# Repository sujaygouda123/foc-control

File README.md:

# FOC CONTROL REV A

BLDC field-oriented-control board for a humanoid robot actuator. KiCad 10, Ø80 mm, 8 layers, 1.6 mm.

| Top | Bottom |
|---|---|
|  |  |

## Main parts

| Function | Part |
|---|---|
| MCU | STM32G474RET3 |
| Gate driver | DRV8353S |
| MOSFETs | 6 × BSC040N10NS5 (100 V, 4 mΩ) |
| Current sensing | 3 × 1 mΩ low-side shunts |
| Position | AS5047P magnetic encoder (bottom side) |
| CAN FD | MCP2562FD, 2 × XT30PW 2+2 (power + CAN) |
| Supplies | 2 × LM5164 (12 V, 5 V), AP2112K (3.3 V) |

## Stage 1 – single actuator

## Stage 2 – multiple actuators

- One cable per link: VBUS + GND (16 AWG) and CAN-H / CAN-L as a twisted pair.
- Two XT30 2+2 connectors per board (IN, OUT), 15 A continuous.
- 120 Ω termination only at the two ends of each bus (JP1 on the last actuator).

## Stackup

| Layer | Use |
|---|---|
| F.Cu, 2 oz | Components, power pours |
| In1 | GND |
| In2 | Signals |
| In3 | VBUS |
| In4 | GND |
| In5 | Signals |
| In6 | GND |
| B.Cu, 2 oz | Phase pours, encoder |

Inner layers are 1 oz. Power runs on the 2 oz outer layers; every signal layer sits next to a plane.

## JLCPCB rules

| Rule | JLCPCB minimum (2 oz) | This board |
|---|---|---|
| Track / gap | 0.15 / 0.15 mm | 0.2 / 0.15 mm (0.15 mm only at fine-pitch pins) |
| Via diameter / hole | 0.25 / 0.15 mm | 0.45 / 0.2 mm |
| Copper to board edge | 0.2 mm | 0.5 mm |

## Trace widths

| Net class | Width | Gap |
|---|---|---|
| Signals | 0.2 mm | 0.15 mm |
| Gate drive | 0.3 mm | 0.15 mm |
| High voltage (VBUS, phases) | 0.5 mm, power in pours | 0.2 mm |
| CAN pair | 0.2 mm | 0.2 mm between the pair |

## File structure

```
foc-control/
├── foc-control.kicad_pro        KiCad 10 project (open this)
├── foc-control.kicad_sch        Root schematic (links the 6 sheets below)
├── can_connectors.kicad_sch     XT30 connectors, MCP2562FD CAN FD transceiver, termination
├── encoder.kicad_sch            AS5047P magnetic encoder
├── MCU.kicad_sch                STM32G474, clock, decoupling, reset/boot, SWD pads
├── power_rails.kicad_sch        12 V and 5 V bucks (LM5164), 3.3 V LDO
├── gate_driver.kicad_sch        DRV8353 gate driver
├── power_stage.kicad_sch        3 half-bridges, shunts, bus capacitors, VBUS sense, NTC
├── foc-control.kicad_pcb        Ø80 mm, 8-layer board layout
├── fp-lib-table                 Project footprint libraries (points to libs/)
├── sym-lib-table                Project symbol libraries (points to libs/)
├── libs/
│   ├── foc-control.kicad_sym    DRV8353 symbol
│   ├── DRV8353.pretty/          DRV8353 footprint (WQFN-40)
│   ├── XT30/                    XT30PW 2+2 symbol, footprint and 3D model
│   └── logo.pretty/             Board logo
├── bom/
│   └── foc-control.csv          Bill of materials
└── docs/
    ├── Stage1/Stage1.drawio.png Stage 1 block diagram (single actuator)
    ├── Stage2/Stage2.drawio.png Stage 2 wiring diagram (multiple actuators)
    └── img/                     3D renders of the board (top, bottom)
```

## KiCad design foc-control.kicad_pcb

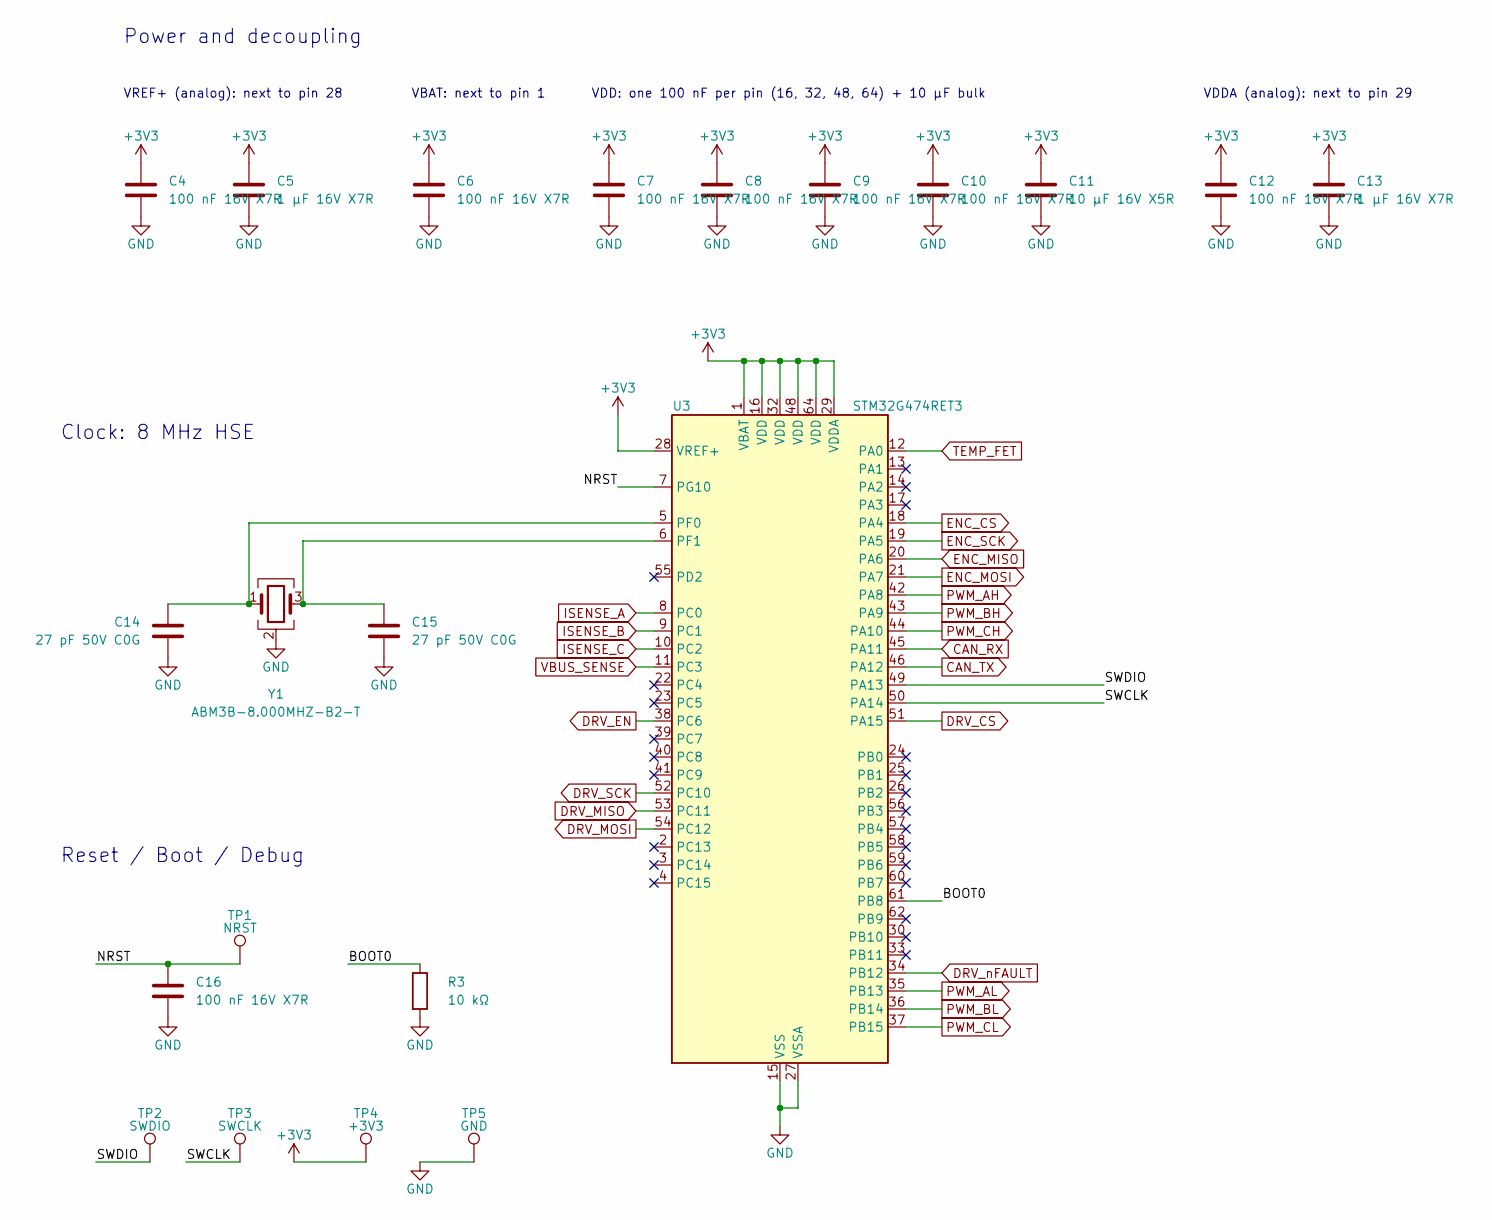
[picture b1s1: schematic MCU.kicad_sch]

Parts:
C4, C6, C7, C8, C9, C10, C12, C16: 100 nF 16V X7R; C_0603_1608Metric
C5, C13: 1 µF 16V X7R; C_0603_1608Metric
C11: 10 µF 16V X5R; C_0603_1608Metric
C14, C15: 27 pF 50V C0G; C_0603_1608Metric
R3: 10 kΩ; R_0603_1608Metric
TP1: NRST; TestPoint_Pad_D1.0mm
TP2: SWDIO; TestPoint_Pad_D1.0mm
TP3: SWCLK; TestPoint_Pad_D1.0mm
TP4: +3V3; TestPoint_Pad_D1.0mm
TP5: GND; TestPoint_Pad_D1.0mm
U3: STM32G474RET3; LQFP-64_10x10mm_P0.5mm
Y1: ABM3B-8.000MHZ-B2-T; Crystal_SMD_Abracon_ABM3B-4Pin_5.0x3.2mm

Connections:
+3V3: C4.1, C5.1, C6.1, C7.1, C8.1, C9.1, C10.1, C11.1, C12.1, C13.1, TP4.1 (1_1), U3.1 (VBAT), U3.16 (VDD), U3.28 (VREF+), U3.29 (VDDA), U3.32 (VDD), U3.48 (VDD), U3.64 (VDD); also elsewhere on the board
/MCU/BOOT0: R3.1, U3.61 (PB8)
/MCU/NRST: C16.1, TP1.1 (1_1), U3.7 (PG10)
/MCU/SWCLK: TP3.1 (1_1), U3.50 (PA14)
/MCU/SWDIO: TP2.1 (1_1), U3.49 (PA13)
CAN_RX: U3.45 (PA11); also elsewhere on the board
CAN_TX: U3.46 (PA12); also elsewhere on the board
DRV_CS: U3.51 (PA15); also elsewhere on the board
DRV_EN: U3.38 (PC6); also elsewhere on the board
DRV_MISO: U3.53 (PC11); also elsewhere on the board
DRV_MOSI: U3.54 (PC12); also elsewhere on the board
DRV_SCK: U3.52 (PC10); also elsewhere on the board
DRV_nFAULT: U3.34 (PB12); also elsewhere on the board
ENC_CS: U3.18 (PA4); also elsewhere on the board
ENC_MISO: U3.20 (PA6); also elsewhere on the board
ENC_MOSI: U3.21 (PA7); also elsewhere on the board
ENC_SCK: U3.19 (PA5); also elsewhere on the board
GND: C4.2, C5.2, C6.2, C7.2, C8.2, C9.2, C10.2, C11.2, C12.2, C13.2, C14.2, C15.2, C16.2, R3.2, TP5.1 (1_1), U3.15 (VSS), U3.27 (VSSA), U3.31 (VSS), U3.47 (VSS), U3.63 (VSS), Y1.2 (G), Y1.4 (G); also elsewhere on the board
ISENSE_A: U3.8 (PC0); also elsewhere on the board
ISENSE_B: U3.9 (PC1); also elsewhere on the board
ISENSE_C: U3.10 (PC2); also elsewhere on the board
unnamed: C14.1, U3.5 (PF0), Y1.1
unnamed: C15.1, U3.6 (PF1), Y1.3
PWM_AH: U3.42 (PA8); also elsewhere on the board
PWM_AL: U3.35 (PB13); also elsewhere on the board
PWM_BH: U3.43 (PA9); also elsewhere on the board
PWM_BL: U3.36 (PB14); also elsewhere on the board
PWM_CH: U3.44 (PA10); also elsewhere on the board
PWM_CL: U3.37 (PB15); also elsewhere on the board
TEMP_FET: U3.12 (PA0); also elsewhere on the board
VBUS_SENSE: U3.11 (PC3); also elsewhere on the board

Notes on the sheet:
Power and decoupling
Clock: 8 MHz HSE
VDDA (analog): next to pin 29
VREF+ (analog): next to pin 28
VBAT: next to pin 1
Reset / Boot / Debug
VDD: one 100 nF per pin (16, 32, 48, 64) + 10 µF bulk

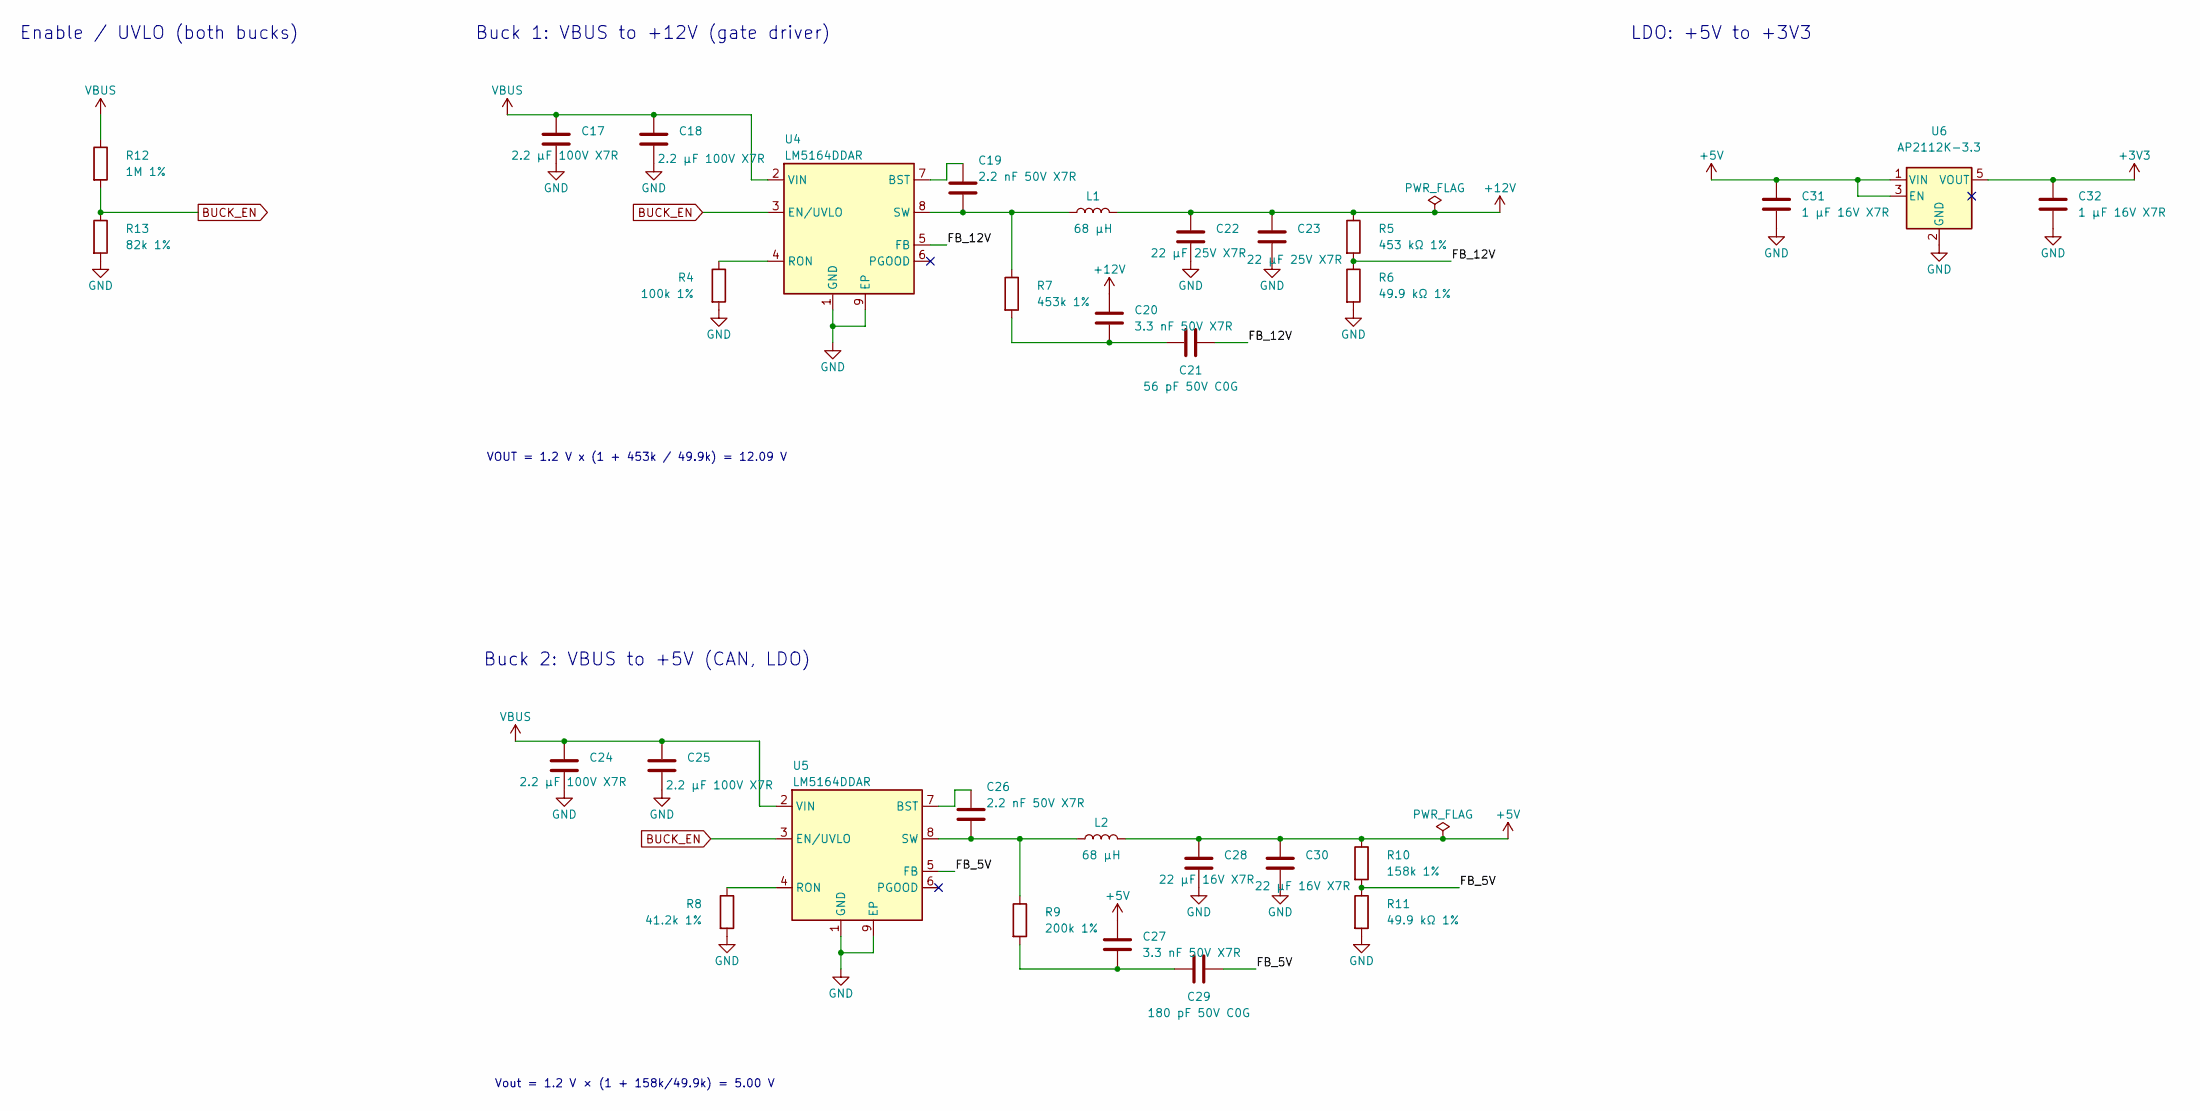
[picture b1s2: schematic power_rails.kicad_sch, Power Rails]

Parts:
C17, C18, C24, C25: 2.2 µF 100V X7R; C_1210_3225Metric
C19, C26: 2.2 nF 50V X7R; C_0603_1608Metric
C20, C27: 3.3 nF 50V X7R; C_0603_1608Metric
C21: 56 pF 50V C0G; C_0603_1608Metric
C22, C23: 22 µF 25V X7R; C_1210_3225Metric
C28, C30: 22 µF 16V X7R; C_1210_3225Metric
C29: 180 pF 50V C0G; C_0603_1608Metric
C31, C32: 1 µF 16V X7R; C_0603_1608Metric
L1, L2: 68 µH; L_Bourns_SRN6045TA; MPN SRN6045TA-680M
R4: 100k 1%; R_0603_1608Metric
R5: 453 kΩ 1%; R_0603_1608Metric
R6, R11: 49.9 kΩ 1%; R_0603_1608Metric
R7: 453k 1%; R_0805_2012Metric
R8: 41.2k 1%; R_0603_1608Metric
R9: 200k 1%; R_0805_2012Metric
R10: 158k 1%; R_0603_1608Metric
R12: 1M 1%; R_0805_2012Metric
R13: 82k 1%; R_0603_1608Metric
U4, U5: LM5164DDAR; HSOP-8-1EP_3.9x4.9mm_P1.27mm_EP2.41x3.1mm_ThermalVias
U6: AP2112K-3.3; SOT-23-5

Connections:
+3V3: C32.1, U6.5 (VOUT); also elsewhere on the board
+5V: C27.1, C28.1, C30.1, C31.1, L2.2, R10.1, U6.1 (VIN), U6.3 (EN); also elsewhere on the board
+12V: C20.1, C22.1, C23.1, L1.2, R5.1; also elsewhere on the board
/Power Rails/FB_5V: C29.2, R10.2, R11.1, U5.5 (FB)
/Power Rails/FB_12V: C21.2, R5.2, R6.1, U4.5 (FB)
BUCK_EN: R12.2, R13.1, U4.3 (EN/UVLO), U5.3 (EN/UVLO)
GND: C17.2, C18.2, C22.2, C23.2, C24.2, C25.2, C28.2, C30.2, C31.2, C32.2, R4.2, R6.2, R8.2, R11.2, R13.2, U4.1 (GND), U4.9 (EP), U5.1 (GND), U5.9 (EP), U6.2 (GND); also elsewhere on the board
unnamed: C20.2, C21.1, R7.2
unnamed: C27.2, C29.1, R9.2
unnamed: C19.1, U4.7 (BST)
unnamed: R4.1, U4.4 (RON)
unnamed: C19.2, L1.1, R7.1, U4.8 (SW)
unnamed: C26.1, U5.7 (BST)
unnamed: R8.1, U5.4 (RON)
unnamed: C26.2, L2.1, R9.1, U5.8 (SW)
VBUS: C17.1, C18.1, C24.1, C25.1, R12.1, U4.2 (VIN), U5.2 (VIN); also elsewhere on the board

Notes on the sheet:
Buck 1: VBUS to +12V (gate driver)
LDO: +5V to +3V3
Enable / UVLO (both bucks)
VOUT = 1.2 V x (1 + 453k / 49.9k) = 12.09 V
Buck 2: VBUS to +5V (CAN, LDO)
Vout = 1.2 V × (1 + 158k/49.9k) = 5.00 V

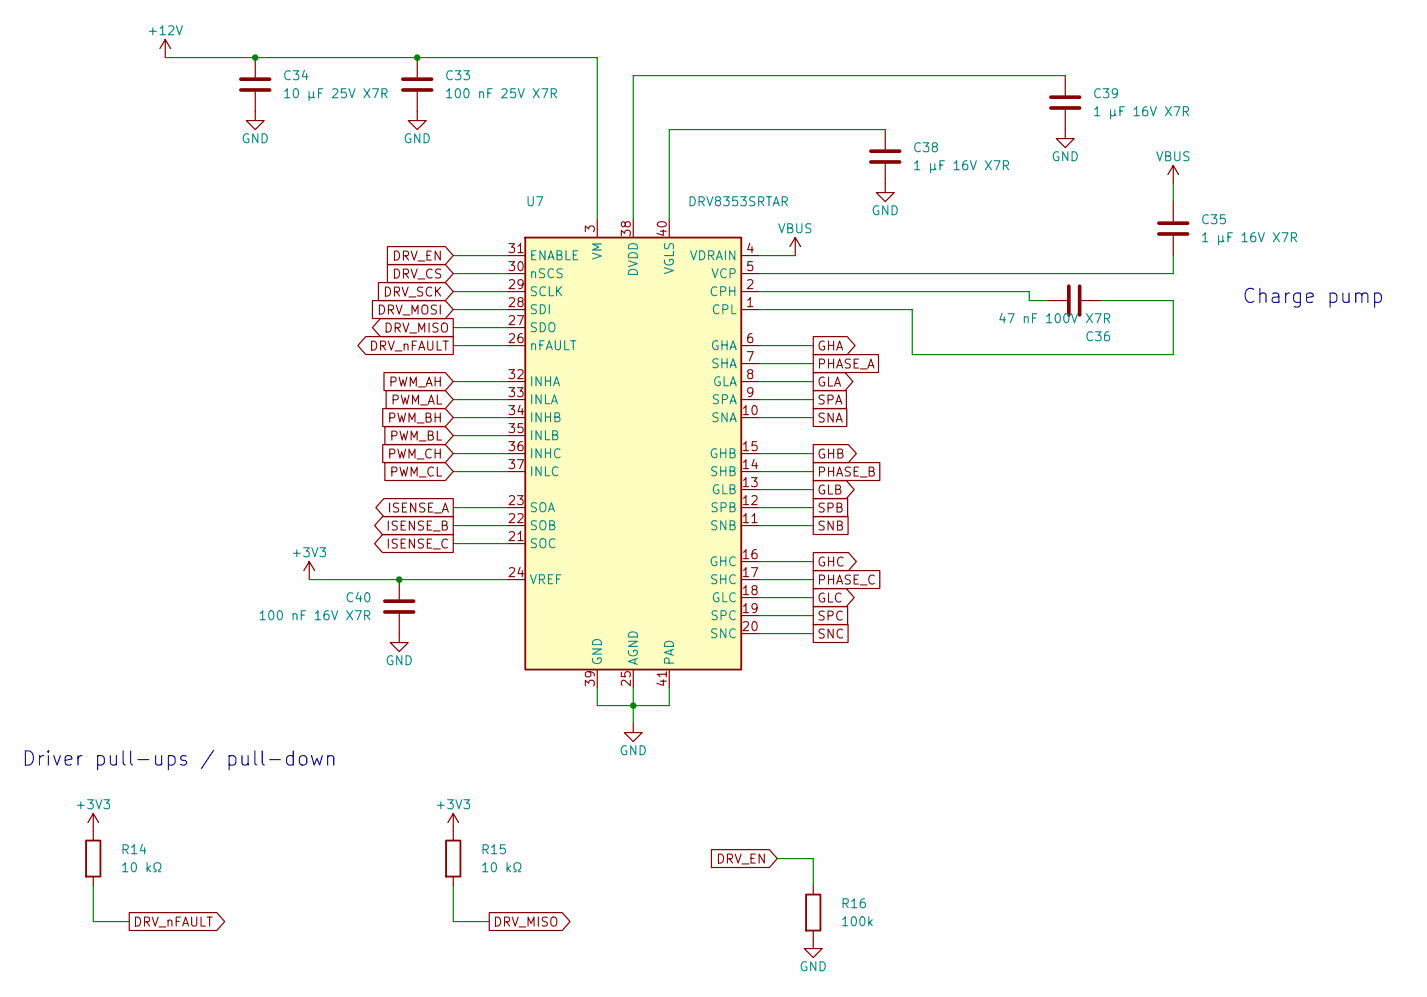
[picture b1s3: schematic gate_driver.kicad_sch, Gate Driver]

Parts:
C33: 100 nF 25V X7R; C_0603_1608Metric
C34: 10 µF 25V X7R; C_1206_3216Metric
C35, C38, C39: 1 µF 16V X7R; C_0603_1608Metric
C36: 47 nF 100V X7R; C_0805_2012Metric
C40: 100 nF 16V X7R; C_0603_1608Metric
R14, R15: 10 kΩ; R_0603_1608Metric
R16: 100k; R_0603_1608Metric
U7: DRV8353SRTAR; RTA0040B

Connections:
+3V3: C40.1, R14.1, R15.1, U7.24 (VREF); also elsewhere on the board
+12V: C33.1, C34.1, U7.3 (VM); also elsewhere on the board
DRV_CS: U7.30 (nSCS); also elsewhere on the board
DRV_EN: R16.1, U7.31 (ENABLE); also elsewhere on the board
DRV_MISO: R15.2, U7.27 (SDO); also elsewhere on the board
DRV_MOSI: U7.28 (SDI); also elsewhere on the board
DRV_SCK: U7.29 (SCLK); also elsewhere on the board
DRV_nFAULT: R14.2, U7.26 (nFAULT); also elsewhere on the board
GHA: U7.6 (GHA); also elsewhere on the board
GHB: U7.15 (GHB); also elsewhere on the board
GHC: U7.16 (GHC); also elsewhere on the board
GLA: U7.8 (GLA); also elsewhere on the board
GLB: U7.13 (GLB); also elsewhere on the board
GLC: U7.18 (GLC); also elsewhere on the board
GND: C33.2, C34.2, C38.2, C39.2, C40.2, R16.2, U7.25 (AGND), U7.39 (GND), U7.41 (PAD); also elsewhere on the board
ISENSE_A: U7.23 (SOA); also elsewhere on the board
ISENSE_B: U7.22 (SOB); also elsewhere on the board
ISENSE_C: U7.21 (SOC); also elsewhere on the board
unnamed: C36.1, U7.2 (CPH)
unnamed: C36.2, U7.1 (CPL)
unnamed: C39.1, U7.38 (DVDD)
unnamed: C35.2, U7.5 (VCP)
unnamed: C38.1, U7.40 (VGLS)
PHASE_A: U7.7 (SHA); also elsewhere on the board
PHASE_B: U7.14 (SHB); also elsewhere on the board
PHASE_C: U7.17 (SHC); also elsewhere on the board
PWM_AH: U7.32 (INHA); also elsewhere on the board
PWM_AL: U7.33 (INLA); also elsewhere on the board
PWM_BH: U7.34 (INHB); also elsewhere on the board
PWM_BL: U7.35 (INLB); also elsewhere on the board
PWM_CH: U7.36 (INHC); also elsewhere on the board
PWM_CL: U7.37 (INLC); also elsewhere on the board
SNA: U7.10 (SNA); also elsewhere on the board
SNB: U7.11 (SNB); also elsewhere on the board
SNC: U7.20 (SNC); also elsewhere on the board
SPA: U7.9 (SPA); also elsewhere on the board
SPB: U7.12 (SPB); also elsewhere on the board
SPC: U7.19 (SPC); also elsewhere on the board
VBUS: C35.1, U7.4 (VDRAIN); also elsewhere on the board

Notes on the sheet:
Driver pull-ups / pull-down
Charge pump

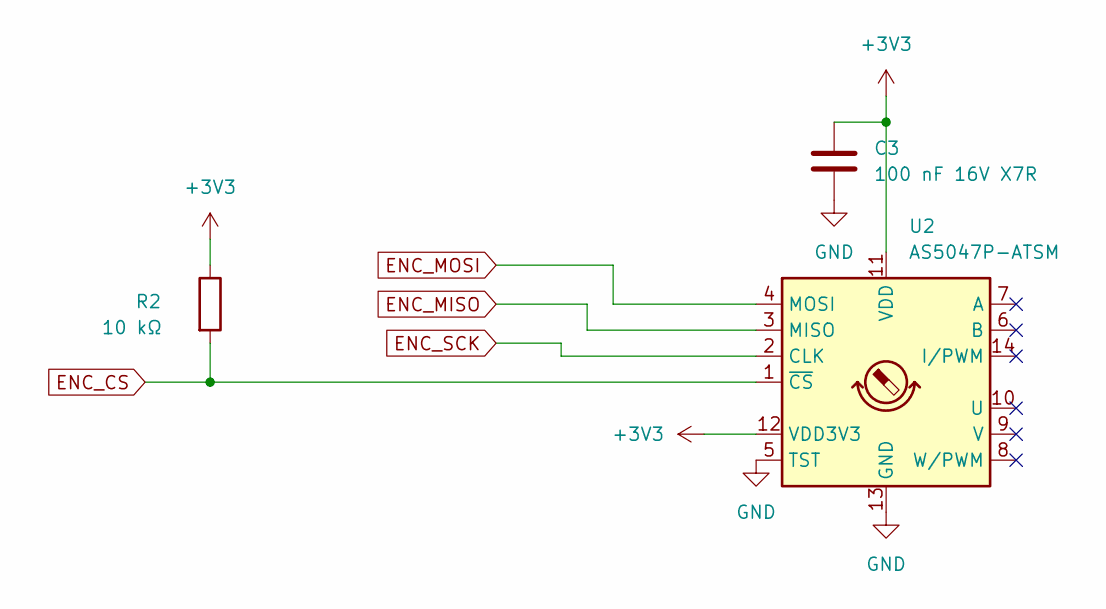
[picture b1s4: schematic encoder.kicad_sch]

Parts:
C3: 100 nF 16V X7R; C_0603_1608Metric
R2: 10 kΩ; R_0603_1608Metric
U2: AS5047P-ATSM; TSSOP-14_4.4x5mm_P0.65mm

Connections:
+3V3: C3.1, R2.1, U2.11 (VDD), U2.12 (VDD3V3); also elsewhere on the board
ENC_CS: R2.2, U2.1 (~CS); also elsewhere on the board
ENC_MISO: U2.3 (MISO); also elsewhere on the board
ENC_MOSI: U2.4 (MOSI); also elsewhere on the board
ENC_SCK: U2.2 (CLK); also elsewhere on the board
GND: C3.2, U2.5 (TST), U2.13 (GND); also elsewhere on the board

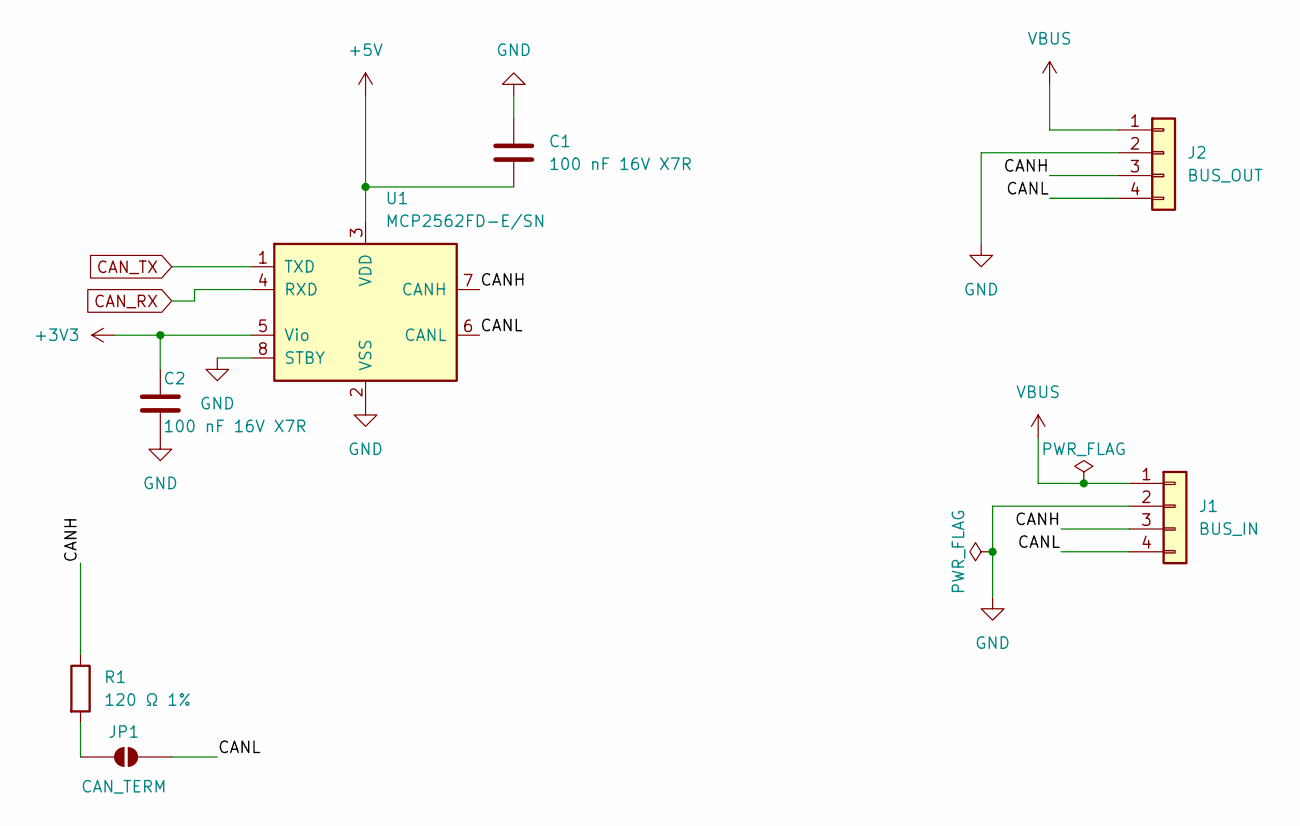
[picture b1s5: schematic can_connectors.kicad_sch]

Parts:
C1, C2: 100 nF 16V X7R; C_0603_1608Metric
J1: BUS_IN; CONN-TH_4P-XT30PW-M; MPN XT30PW(2+2)-M.G.B
J2: BUS_OUT; CONN-TH_4P-XT30PW-M; MPN XT30PW(2+2)-M.G.B
JP1: CAN_TERM; SolderJumper-2_P1.3mm_Open_RoundedPad1.0x1.5mm
R1: 120 Ω 1%; R_0603_1608Metric
U1: MCP2562FD-E/SN; SOIC-8_3.9x4.9mm_P1.27mm

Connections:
+3V3: C2.1, U1.5 (Vio); also elsewhere on the board
+5V: C1.2, U1.3 (VDD); also elsewhere on the board
/CAN + Connectors/CANH: J1.3, J2.3, R1.1, U1.7 (CANH)
/CAN + Connectors/CANL: J1.4, J2.4, JP1.2 (B), U1.6 (CANL)
CAN_RX: U1.4 (RXD); also elsewhere on the board
CAN_TX: U1.1 (TXD); also elsewhere on the board
GND: C1.1, C2.2, J1.2, J2.2, U1.2 (VSS), U1.8 (STBY); also elsewhere on the board
unnamed: JP1.1 (A), R1.2
VBUS: J1.1, J2.1; also elsewhere on the board

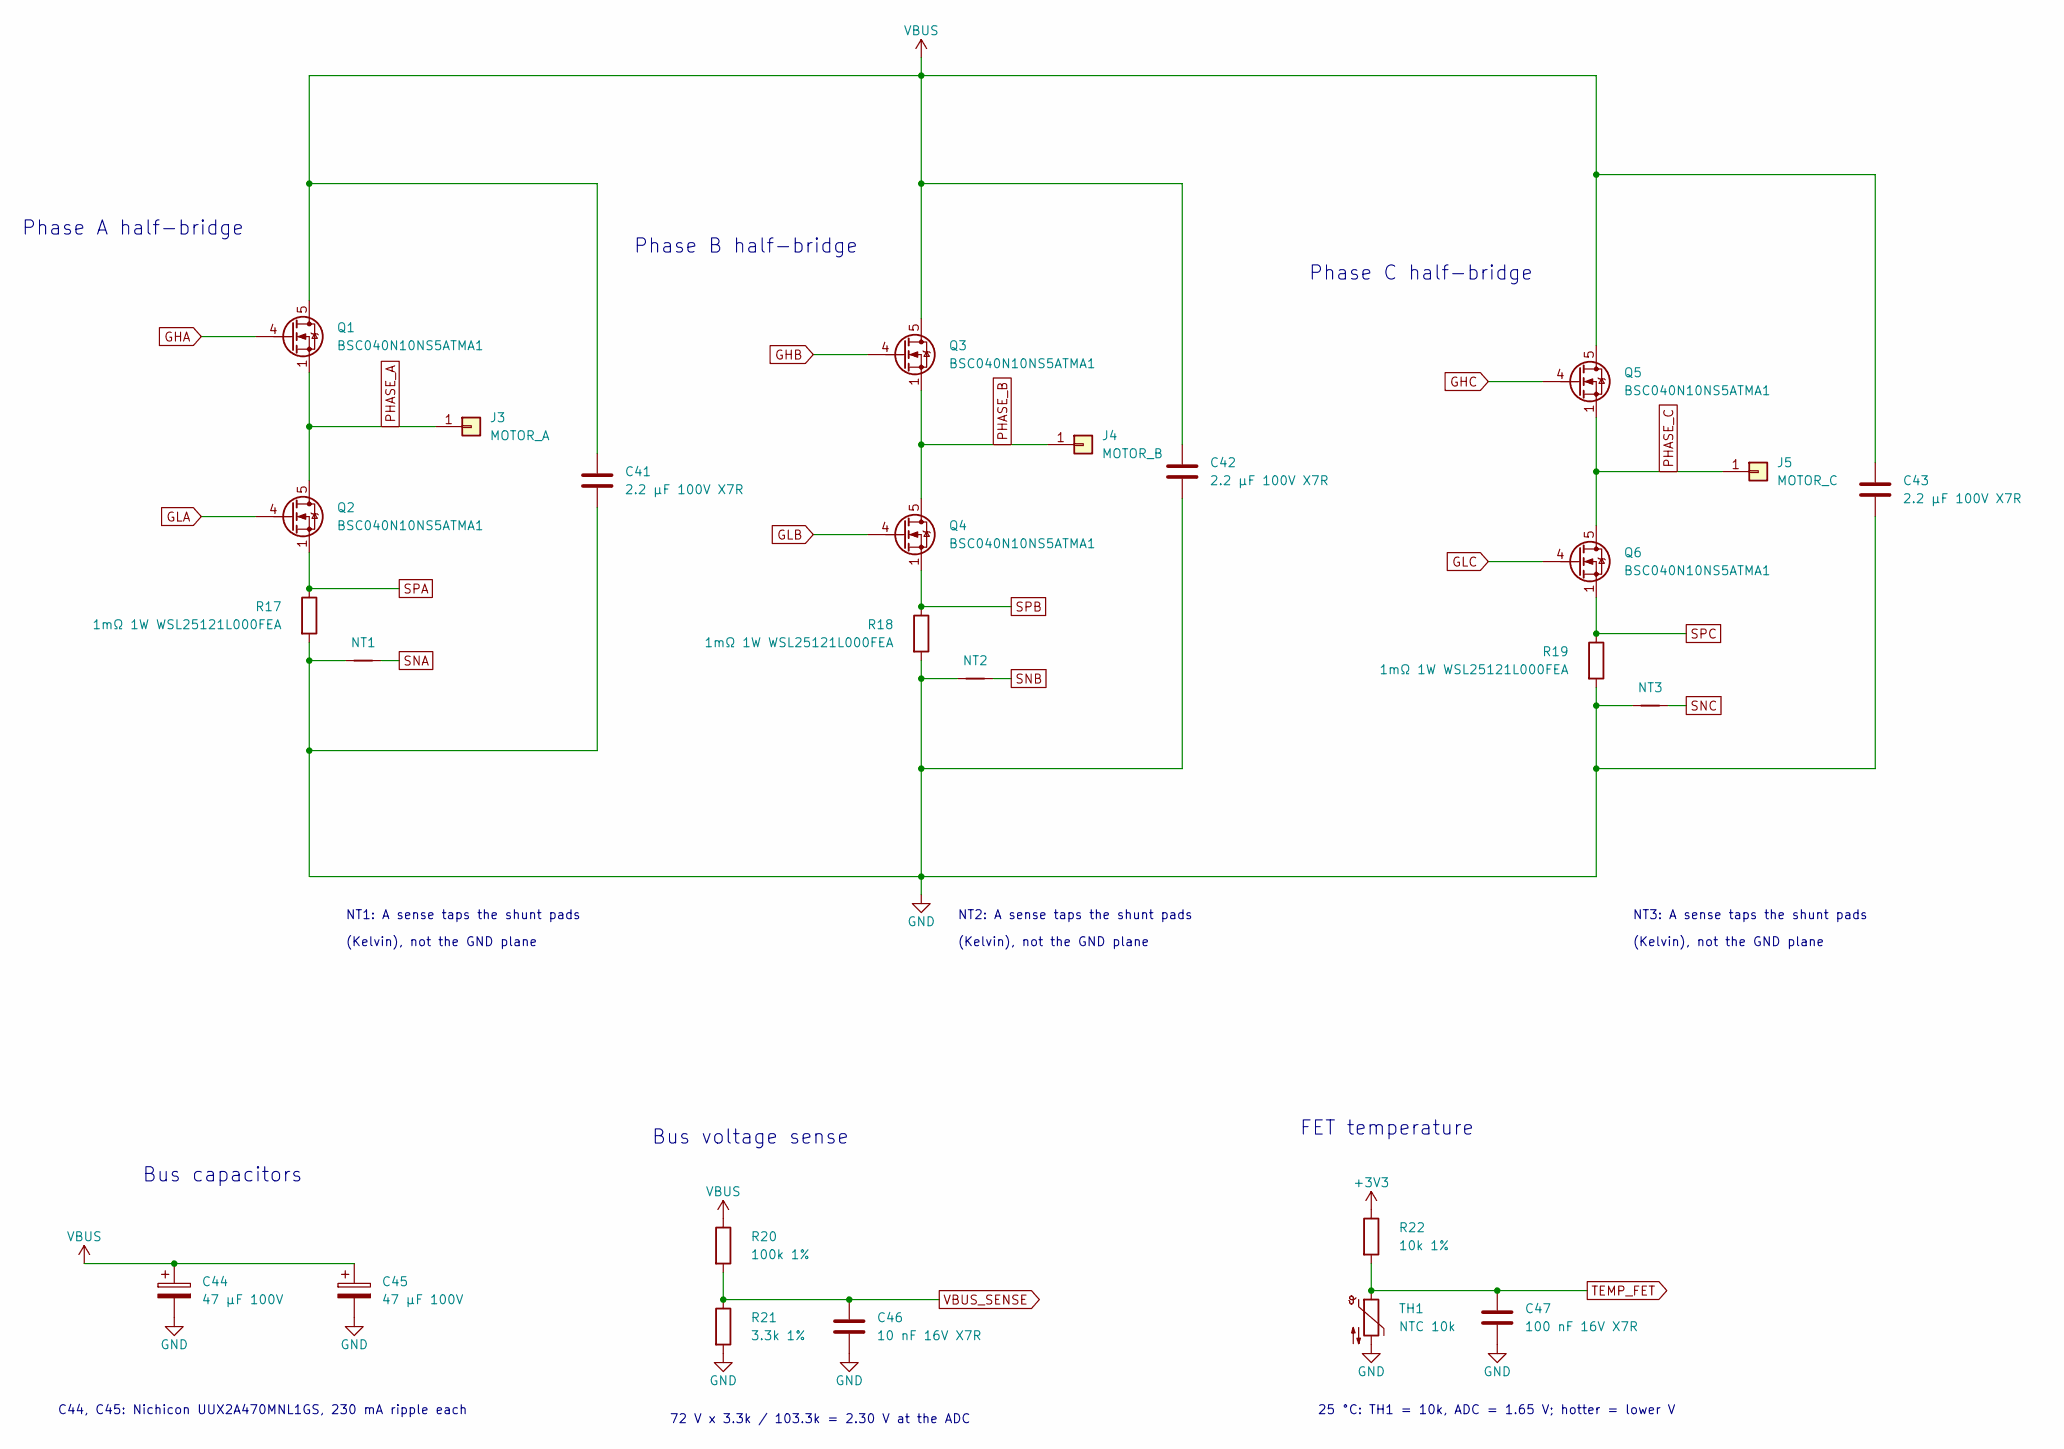
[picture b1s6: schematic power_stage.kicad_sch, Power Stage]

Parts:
C41, C42, C43: 2.2 µF 100V X7R; C_1210_3225Metric
C44, C45: 47 µF 100V; CP_Elec_10x10; MPN UUX2A470MNL1GS
C46: 10 nF 16V X7R; C_0603_1608Metric
C47: 100 nF 16V X7R; C_0603_1608Metric
J3: MOTOR_A; SolderWire-1.5sqmm_1x01_D1.7mm_OD3.9mm
J4: MOTOR_B; SolderWire-1.5sqmm_1x01_D1.7mm_OD3.9mm
J5: MOTOR_C; SolderWire-1.5sqmm_1x01_D1.7mm_OD3.9mm
NT1, NT2, NT3: NetTie_2; NetTie-2_SMD_Pad0.5mm
Q1, Q2, Q3, Q4, Q5, Q6: BSC040N10NS5ATMA1; TDSON-8-1
R17, R18, R19: 1mΩ 1W WSL25121L000FEA; R_2512_6332Metric
R20: 100k 1%; R_1206_3216Metric
R21: 3.3k 1%; R_0603_1608Metric
R22: 10k 1%; R_0603_1608Metric
TH1: NTC 10k; R_0603_1608Metric; MPN NCP18XH103F03RB

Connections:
+3V3: R22.1; also elsewhere on the board
GHA: Q1.4 (G); also elsewhere on the board
GHB: Q3.4 (G); also elsewhere on the board
GHC: Q5.4 (G); also elsewhere on the board
GLA: Q2.4 (G); also elsewhere on the board
GLB: Q4.4 (G); also elsewhere on the board
GLC: Q6.4 (G); also elsewhere on the board
GND: C41.2, C42.2, C43.2, C44.2, C45.2, C46.2, C47.2, NT1.1, NT2.1, NT3.1, R17.2, R18.2, R19.2, R21.2, TH1.2; also elsewhere on the board
PHASE_A: J3.1 (Pin_1_1), Q1.1 (S), Q1.2 (S), Q1.3 (S), Q2.5 (D); also elsewhere on the board
PHASE_B: J4.1 (Pin_1_1), Q3.1 (S), Q3.2 (S), Q3.3 (S), Q4.5 (D); also elsewhere on the board
PHASE_C: J5.1 (Pin_1_1), Q5.1 (S), Q5.2 (S), Q5.3 (S), Q6.5 (D); also elsewhere on the board
SNA: NT1.2; also elsewhere on the board
SNB: NT2.2; also elsewhere on the board
SNC: NT3.2; also elsewhere on the board
SPA: Q2.1 (S), Q2.2 (S), Q2.3 (S), R17.1; also elsewhere on the board
SPB: Q4.1 (S), Q4.2 (S), Q4.3 (S), R18.1; also elsewhere on the board
SPC: Q6.1 (S), Q6.2 (S), Q6.3 (S), R19.1; also elsewhere on the board
TEMP_FET: C47.1, R22.2, TH1.1; also elsewhere on the board
VBUS: C41.1, C42.1, C43.1, C44.1, C45.1, Q1.5 (D), Q3.5 (D), Q5.5 (D), R20.1; also elsewhere on the board
VBUS_SENSE: C46.1, R20.2, R21.1; also elsewhere on the board

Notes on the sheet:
(Kelvin), not the GND plane
72 V x 3.3k / 103.3k = 2.30 V at the ADC
Bus capacitors
NT3: A sense taps the shunt pads
Phase B half-bridge
Phase A half-bridge
25 °C: TH1 = 10k, ADC = 1.65 V; hotter = lower V
Bus voltage sense
NT2: A sense taps the shunt pads
Phase C half-bridge
C44, C45: Nichicon UUX2A470MNL1GS, 230 mA ripple each
NT1: A sense taps the shunt pads
FET temperature

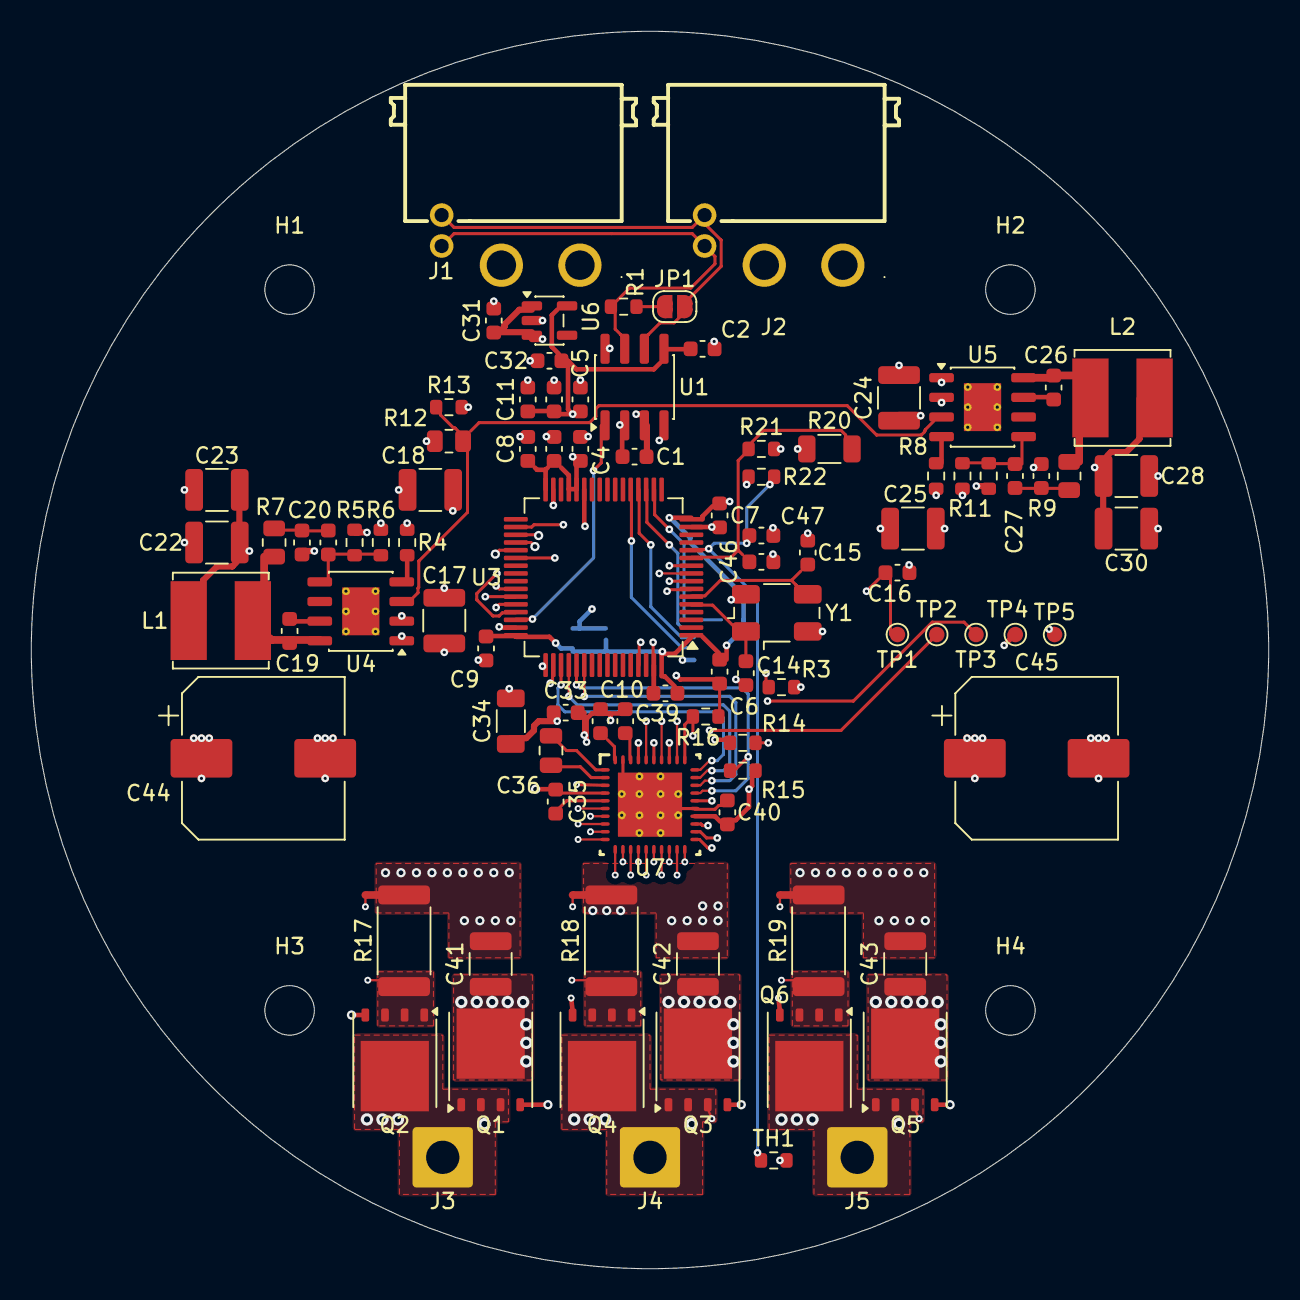
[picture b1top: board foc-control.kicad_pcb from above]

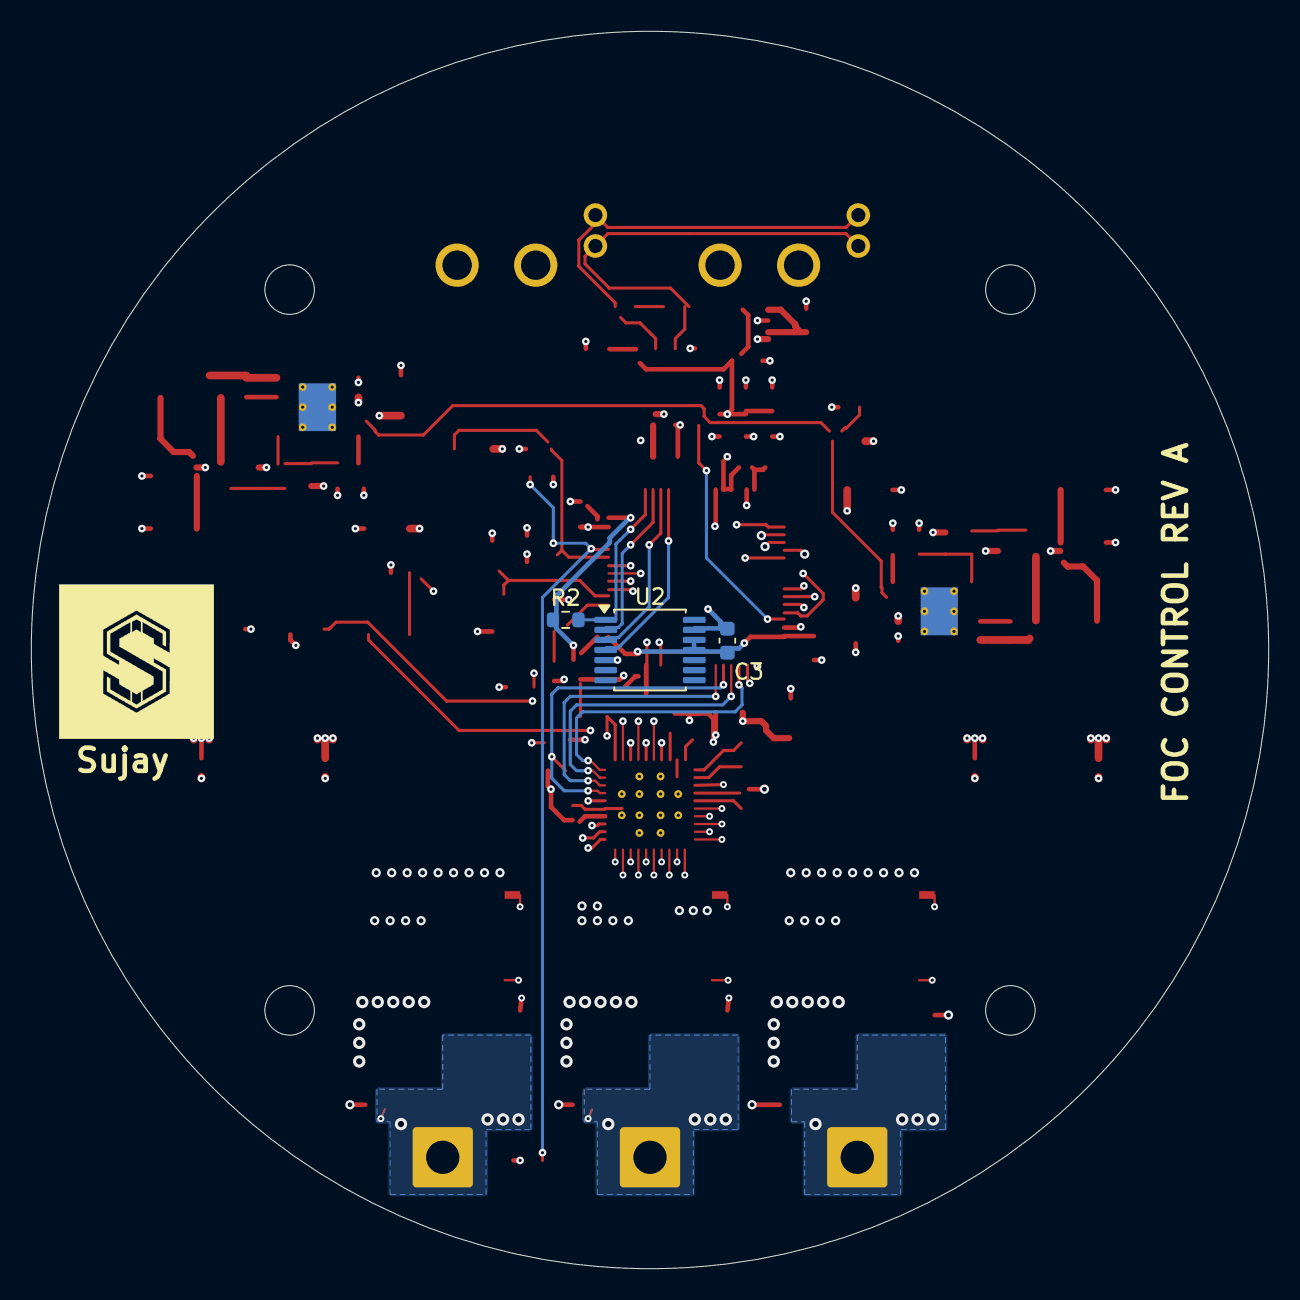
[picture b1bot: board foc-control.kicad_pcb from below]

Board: 8 copper layers, 80.0 x 80.0 mm, 103 parts (3 on the bottom side), 68 nets.

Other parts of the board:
H1, H2, H3, H4: MountingHole_3.2mm_M3
